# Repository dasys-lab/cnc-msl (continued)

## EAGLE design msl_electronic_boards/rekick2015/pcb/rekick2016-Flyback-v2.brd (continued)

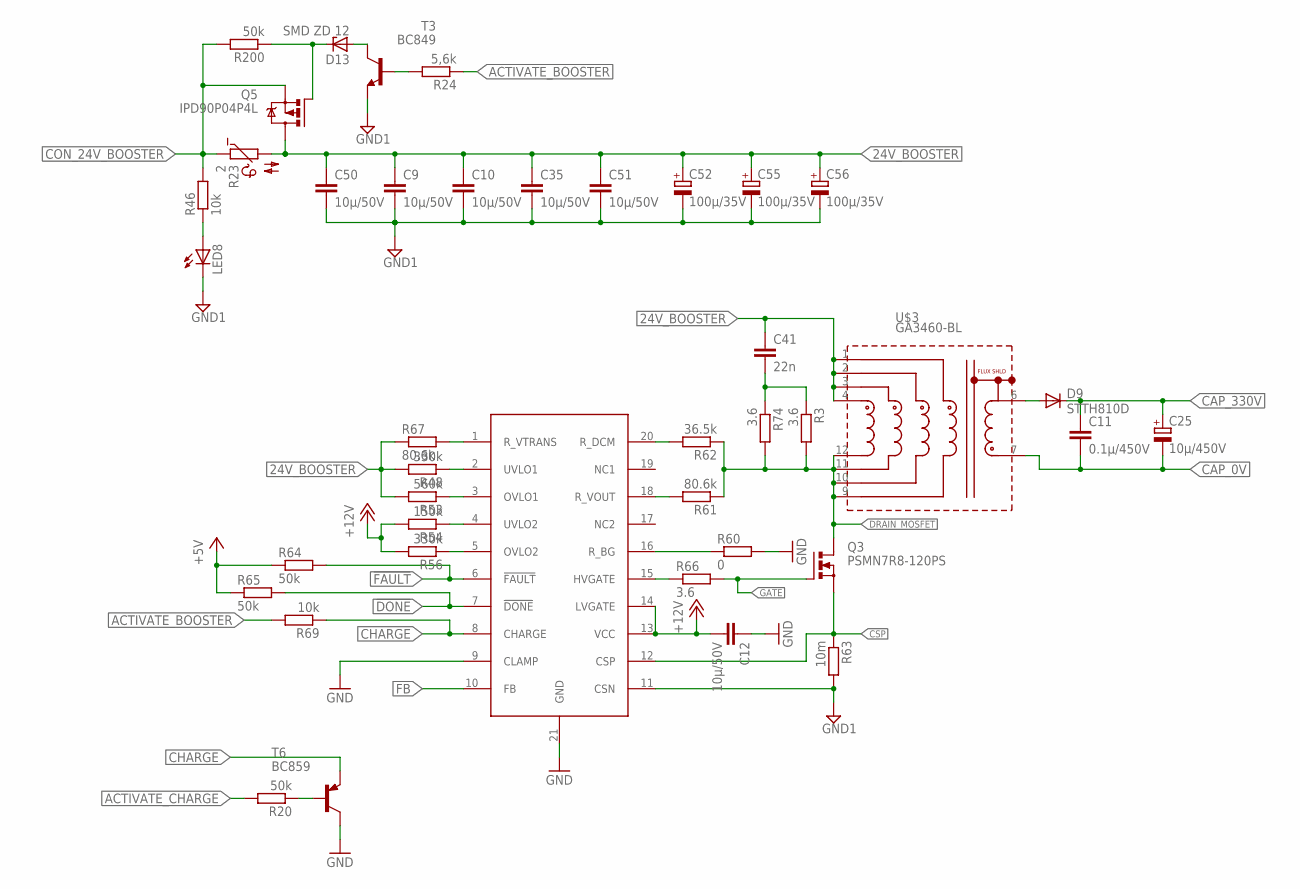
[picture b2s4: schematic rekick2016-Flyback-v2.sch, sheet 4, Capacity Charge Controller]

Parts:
C9, C10, C12, C35, C50, C51: 10µ/50V; C1206
C11: 0.1µ/450V; C2220K
C25: 10µ/450V; E5-10,5
C41: 22n; C1206
C52, C55, C56: 100µ/35V; E2,5-7
D9: STTH810D; TO220ACS
D13: SMD ZD 12; TO236
LED8: LEDCHIP-LED0805; CHIP-LED0805
Q3: PSMN7R8-120PS; TO220BV
Q5: IPD90P04P4L; D-PAK_TO252AA
R3, R66, R74: 3.6; R2010
R20, R64, R65, R200: 50k; R0805
R23: 2; N644A
R24: 5,6k; R0805
R46, R69: 10k; R0805
R48, R56: 330k; R0805
R53: 560k; R0805
R54: 150k; R0805
R60: 0; R0805
R61, R67: 80.6k; R0805
R62: 36.5k; R0805
R63: 10m; R2818
T3: BC849; SOT23
T6: BC859; SOT23-BEC
U$3: GA3460-BL; GA3459
U$9: LT3751; TSSOP20

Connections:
24V_BOOSTER: C9.1, C10.1, C35.1, C41.1, C50.1, C51.1, C52.+, C55.+, C56.+, Q5.4 (D), R23.2, R48.2, R53.2, R67.1, U$3.1 (W11), U$3.2 (W21), U$3.3 (W31), U$3.4 (W41); also elsewhere on the board
!DONE: R65.2, U$9.7 (!DONE); also elsewhere on the board
!FAULT: R64.2, U$9.6 (!FAULT); also elsewhere on the board
+5V: R64.1, R65.1; also elsewhere on the board
+12V: C12.2, R54.2, R56.2, U$9.13 (VCC), U$9.14 (LVGATE); also elsewhere on the board
ACTIVATE_BOOSTER: R24.1, R69.2; also elsewhere on the board
ACTIVATE_CHARGE: R20.2; also elsewhere on the board
CAP_0V: C11.2, C25.-, U$3.7 (S2); also elsewhere on the board
CAP_330V: C11.1, C25.+, D9.C; also elsewhere on the board
CHARGE: R69.1, T6.E, U$9.8 (CHARGE); also elsewhere on the board
CON_24V_BOOSTER: Q5.3 (S), R23.1, R46.2, R200.2; also elsewhere on the board
CSP: Q3.S, R63.P$1 (1), U$9.12 (CSP); also elsewhere on the board
DRAIN_MOSFET: Q3.D, R3.2, R61.1, R62.1, R74.2, U$3.9 (W12), U$3.10 (W22), U$3.11 (W32), U$3.12 (W42); also elsewhere on the board
FB: U$9.10 (FB); also elsewhere on the board
GATE: Q3.G, R66.2; also elsewhere on the board
GND: C12.1, R60.2, T6.C, U$9.9 (CLAMP), U$9.21 (GND); also elsewhere on the board
GND1: C9.2, C10.2, C35.2, C50.2, C51.2, C52.-, C55.-, C56.-, LED8.C, R63.P$2 (2), T3.2 (E), U$9.11 (CSN); also elsewhere on the board
unnamed: R60.1, U$9.16 (R_BG)
unnamed: R66.1, U$9.15 (HVGATE)
unnamed: R20.1, T6.B
unnamed: D9.A, U$3.6 (S1)
unnamed: R67.2, U$9.1 (R_VTRANS)
unnamed: R61.2, U$9.18 (R_VOUT)
unnamed: R62.2, U$9.20 (R_DCM)
unnamed: R54.1, U$9.4 (UVLO2)
unnamed: R53.1, U$9.3 (OVLO1)
unnamed: D13.C, Q5.1 (G), R200.1
unnamed: D13.A, T3.3 (C)
unnamed: R24.2, T3.1 (B)
unnamed: R56.1, U$9.5 (OVLO2)
unnamed: R48.1, U$9.2 (UVLO1)
unnamed: LED8.A, R46.1
unnamed: C41.2, R3.1, R74.1

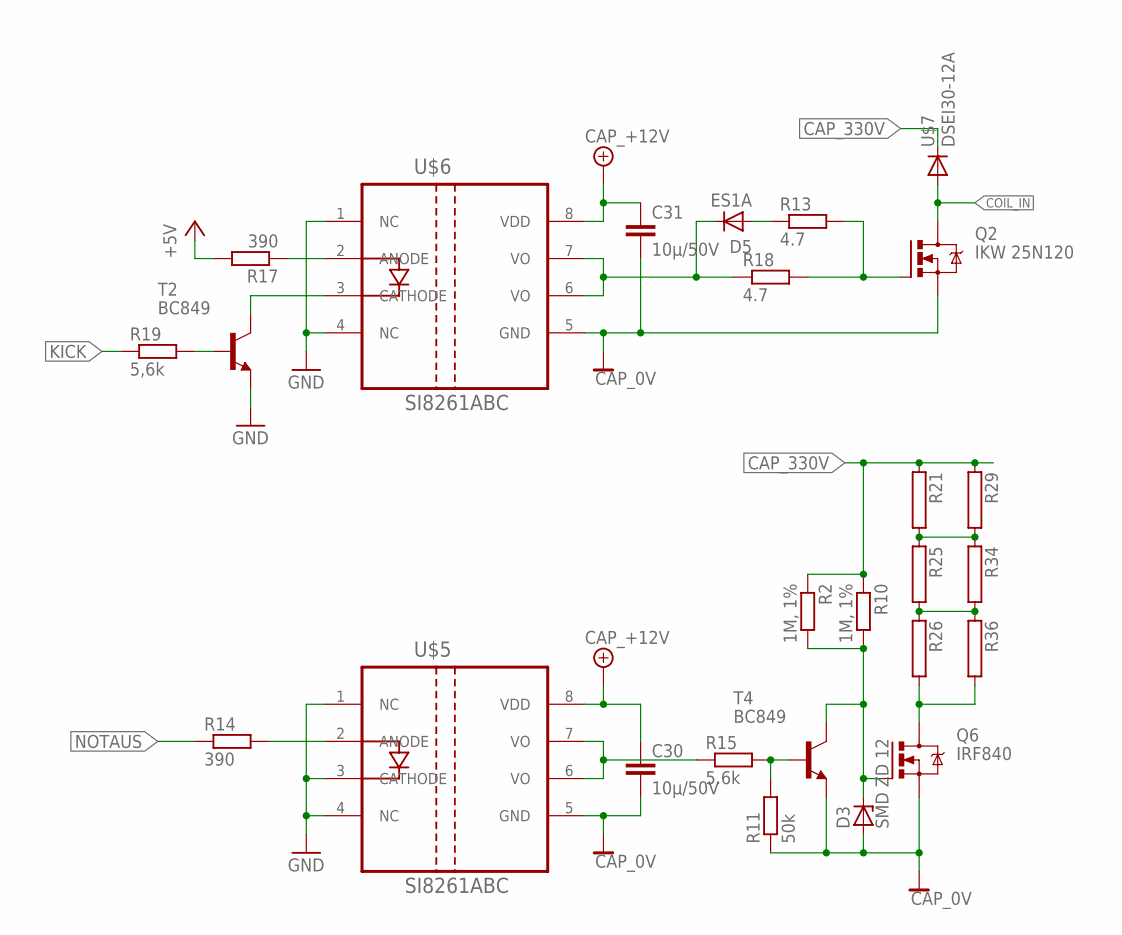
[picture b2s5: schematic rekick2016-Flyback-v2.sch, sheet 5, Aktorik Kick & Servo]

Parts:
C30, C31: 10µ/50V; C1206
D3: SMD ZD 12; TO236
D5: ES1A; SMA-DO214AC
Q2: IKW 25N120; TO247BV
Q6: IRF840; TO220BV
R2, R10: 1M, 1%; R1206
R11: 50k; R0805
R13, R18: 4.7; R0805
R14, R17: 390; R0805
R15: 5.6k; R0805
R19: 5,6k; R0805
R21, R25, R26, R29, R34, R36: RKH214-8R; KH214R-8
T2, T4: BC849; SOT23
U$5, U$6: SI8261ABC; SOIC-8
U$7: DSEI30-12A; TO247AD

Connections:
+5V: R17.2; also elsewhere on the board
CAP_0V: C30.2, C31.2, D3.A, Q2.S, Q6.S, R11.1, T4.2 (E), U$5.5 (GND), U$6.5 (GND); also elsewhere on the board
CAP_330V: R2.1, R10.1, R21.1, R29.1, U$7.C; also elsewhere on the board
CAP_+12V: C30.1, C31.1, U$5.8 (VDD), U$6.8 (VDD); also elsewhere on the board
COIL_IN: Q2.D, U$7.A; also elsewhere on the board
GND: T2.2 (E), U$5.1 (NC), U$5.3 (CATHODE), U$5.4 (NC), U$6.1 (NC), U$6.4 (NC); also elsewhere on the board
KICK: R19.1; also elsewhere on the board
unnamed: R25.2, R26.1, R34.2, R36.1
unnamed: R21.2, R25.1, R29.2, R34.1
unnamed: D3.C, Q6.G, R2.2, R10.2, T4.3 (C)
unnamed: R14.2, U$5.2 (ANODE)
unnamed: R15.1, U$5.6 (VO), U$5.7 (VO)
unnamed: R17.1, U$6.2 (ANODE)
unnamed: D5.K (C), R18.1, U$6.6 (VO), U$6.7 (VO)
unnamed: T2.3 (C), U$6.3 (CATHODE)
unnamed: R11.2, R15.2, T4.1 (B)
unnamed: R19.2, T2.1 (B)
unnamed: Q2.G, R13.2, R18.2
unnamed: Q6.D, R26.2, R36.2
unnamed: D5.A, R13.1
NOTAUS: R14.1; also elsewhere on the board

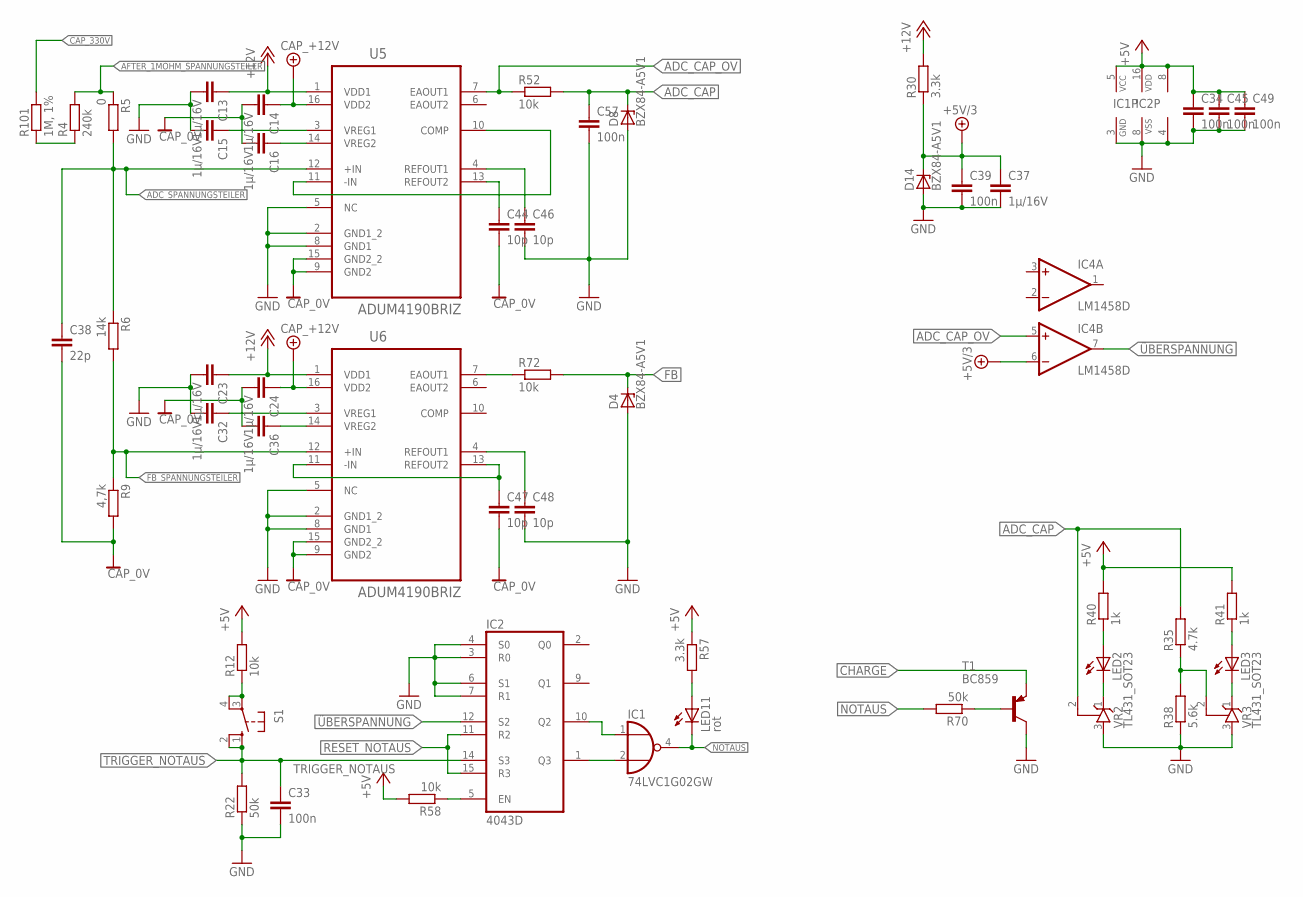
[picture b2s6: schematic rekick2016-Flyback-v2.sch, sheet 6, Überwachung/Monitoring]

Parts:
C13, C14, C15, C16, C23, C24, C32, C36, C37: 1µ/16V; C0603
C33, C34, C39, C45, C49, C57: 100n; C0603
C38: 22p; C0603
C44, C46, C47, C48: 10p; C0603
D4, D8, D14: BZX84-A5V1; TO236
IC1: 74LVC1G02GW; SOT23-5
IC2: 4043D; SO16
IC4: LM1458D; SO08
LED2, LED3: LEDCHIP-LED0805; CHIP-LED0805
LED11: rot; CHIPLED_0603
R4: 240k; R0805
R5: 0; R0805
R6: 14k; R0805
R9: 4,7k; R0805
R12, R52, R58, R72: 10k; R0805
R22, R70: 50k; R0805
R30, R57: 3.3k; R0805
R35: 4.7k; R0805
R38: 5.6k; R0805
R40, R41: 1k; R0805
R101: 1M, 1%; R1206
S1: 10-XX; B3F-10XX
T1: BC859; SOT23-BEC
U5, U6: ADUM4190BRIZ; SOIC127P1032X265-16N
VR2, VR3: TL431_SOT23; SOT23

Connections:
+5V: C34.1, C45.1, C49.1, IC1.5 (VCC), IC2.16 (VDD), IC4.8 (V+), R12.2, R40.2, R41.2, R57.1, R58.2; also elsewhere on the board
+5V/3: C37.1, C39.1, D14.C, IC4.6 (-IN), R30.1
+12V: C13.1, C23.1, R30.2, U5.1 (VDD1), U6.1 (VDD1); also elsewhere on the board
ADC_CAP: C57.1, D8.C, R35.2, R52.2, VR2.2 (R); also elsewhere on the board
ADC_CAP_OV: IC4.5 (+IN), R52.1, U5.7 (EAOUT1)
ADC_SPANNUNGSTEILER: C38.1, R5.2, R6.1, U5.12 (+IN); also elsewhere on the board
AFTER_1MOHM_SPANNUNGSTEILER: R4.2, R5.1; also elsewhere on the board
CAP_0V: C14.2, C16.2, C24.2, C36.2, C38.2, C44.2, C47.2, R9.2, U5.9 (GND2), U5.15 (GND2_2), U6.9 (GND2), U6.15 (GND2_2); also elsewhere on the board
CAP_330V: R101.2; also elsewhere on the board
CAP_+12V: C14.1, C24.1, U5.16 (VDD2), U6.16 (VDD2); also elsewhere on the board
CHARGE: T1.E; also elsewhere on the board
FB: D4.C, R72.2; also elsewhere on the board
FB_SPANNUNGSTEILER: R6.2, R9.1, U6.12 (+IN); also elsewhere on the board
GND: C13.2, C15.2, C23.2, C32.2, C33.2, C34.2, C37.2, C39.2, C45.2, C46.2, C48.2, C49.2, C57.2, D4.A, D8.A, D14.A, IC1.3 (GND), IC2.3 (R0), IC2.4 (S0), IC2.6 (S1), IC2.7 (R1), IC2.8 (VSS), IC4.4 (V-), R22.1, R38.1, T1.C, U5.2 (GND1_2), U5.5 (NC), U5.8 (GND1), U6.2 (GND1_2), U6.5 (NC), U6.8 (GND1), VR2.3 (A), VR3.3 (A); also elsewhere on the board
unnamed: R4.1, R101.1
unnamed: U5.10 (COMP), U5.11 (-IN)
unnamed: R12.1, S1.3, S1.4 (P1)
unnamed: IC1.1 (I0), IC2.10 (Q2)
unnamed: IC1.2 (I1), IC2.1 (Q3)
unnamed: IC2.5 (EN), R58.1
unnamed: C15.1, U5.3 (VREG1)
unnamed: C16.1, U5.14 (VREG2)
unnamed: C36.1, U6.14 (VREG2)
unnamed: R35.1, R38.2, VR3.2 (R)
unnamed: LED2.C, VR2.1 (C)
unnamed: LED3.C, VR3.1 (C)
unnamed: LED2.A, R40.1
unnamed: LED3.A, R41.1
unnamed: C32.1, U6.3 (VREG1)
unnamed: LED11.A, R57.2
unnamed: R70.1, T1.B
unnamed: C47.1, U6.11 (-IN), U6.13 (REFOUT2)
unnamed: C44.1, U5.13 (REFOUT2)
unnamed: C46.1, U5.4 (REFOUT1)
unnamed: R72.1, U6.7 (EAOUT1)
unnamed: C48.1, U6.4 (REFOUT1)
NOTAUS: IC1.4 (O), LED11.C, R70.2; also elsewhere on the board
RESET_NOTAUS: IC2.11 (R2), IC2.15 (R3); also elsewhere on the board
TRIGGER_NOTAUS: C33.1, IC2.14 (S3), R22.2, S1.1 (S), S1.2 (S1); also elsewhere on the board
ÜBERSPANNUNG: IC2.12 (S2), IC4.7 (OUT)

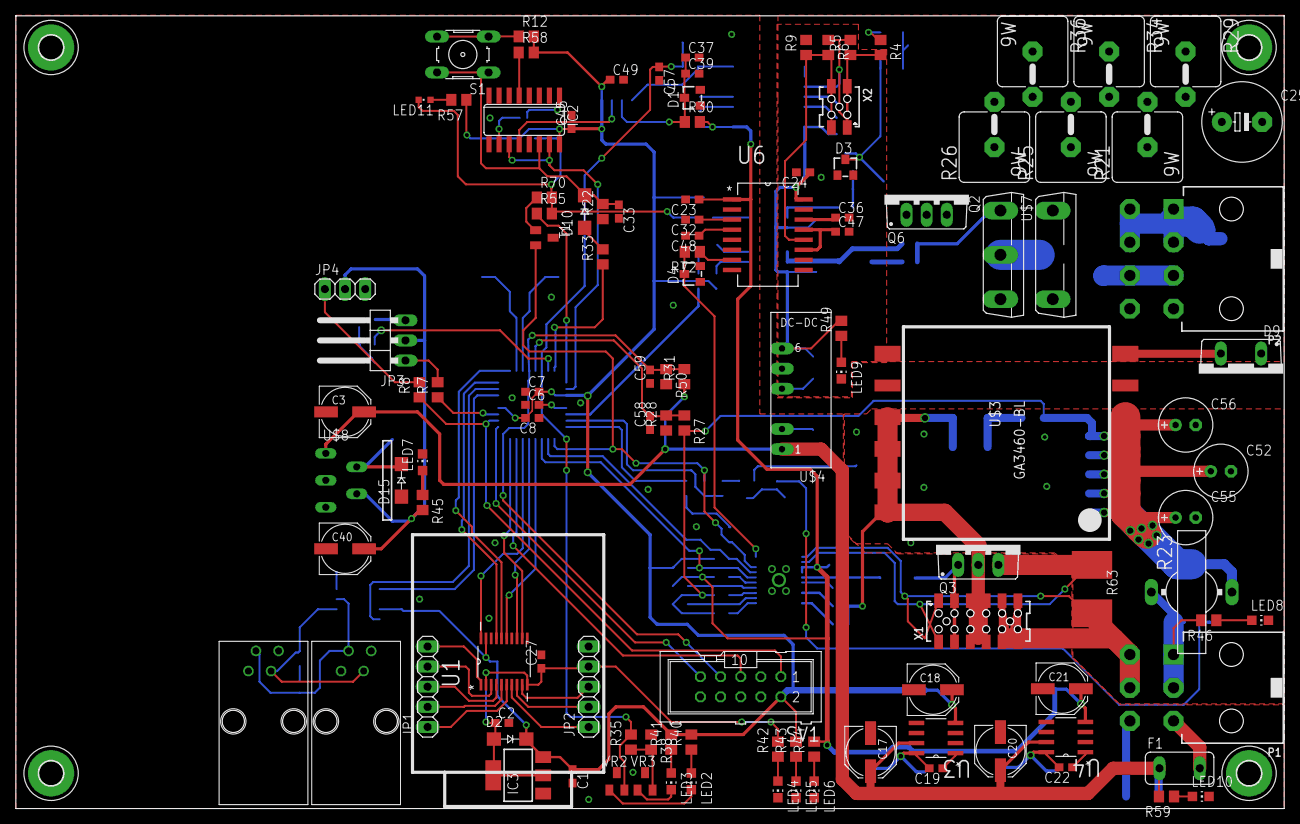
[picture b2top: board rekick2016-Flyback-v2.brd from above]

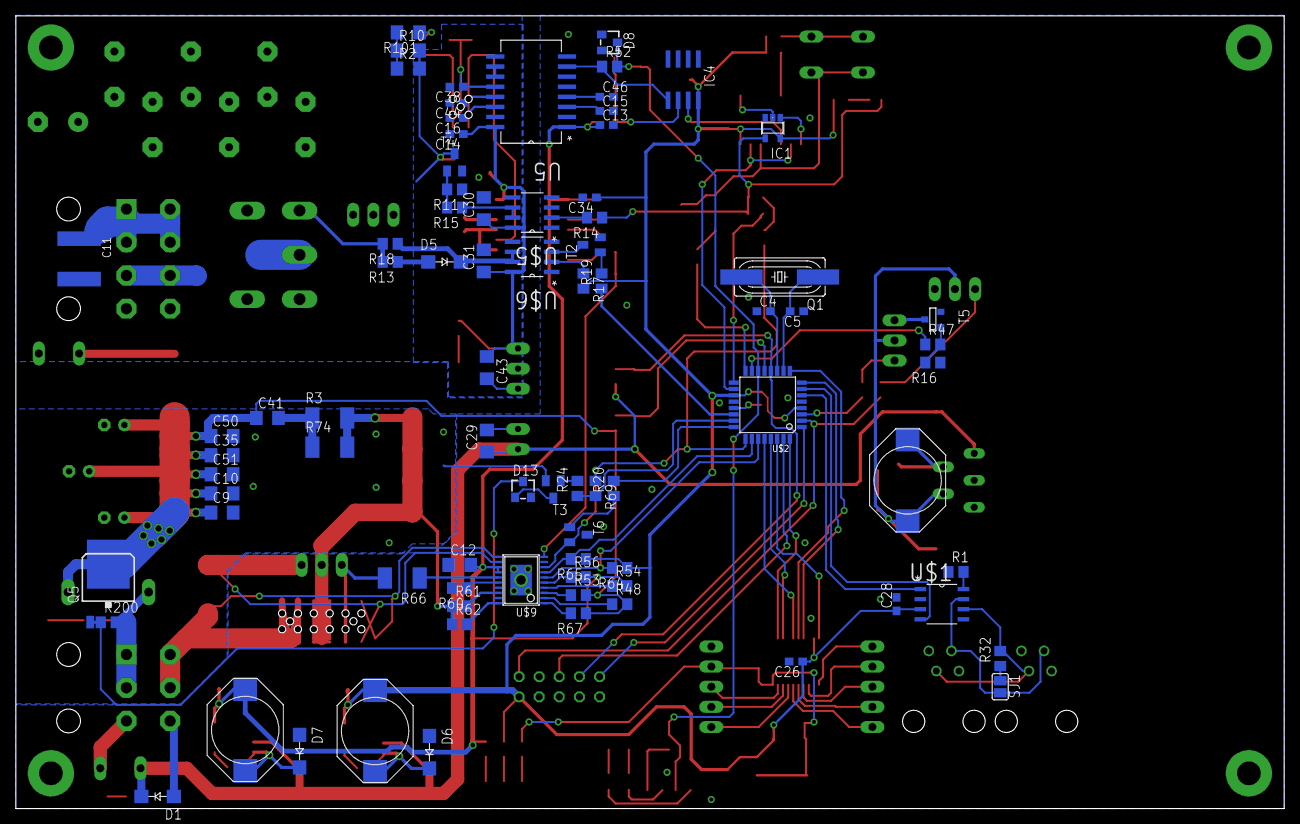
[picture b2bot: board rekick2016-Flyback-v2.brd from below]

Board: 4 copper layers, 160.0 x 100.0 mm, 201 parts (81 on the bottom side), 133 nets.

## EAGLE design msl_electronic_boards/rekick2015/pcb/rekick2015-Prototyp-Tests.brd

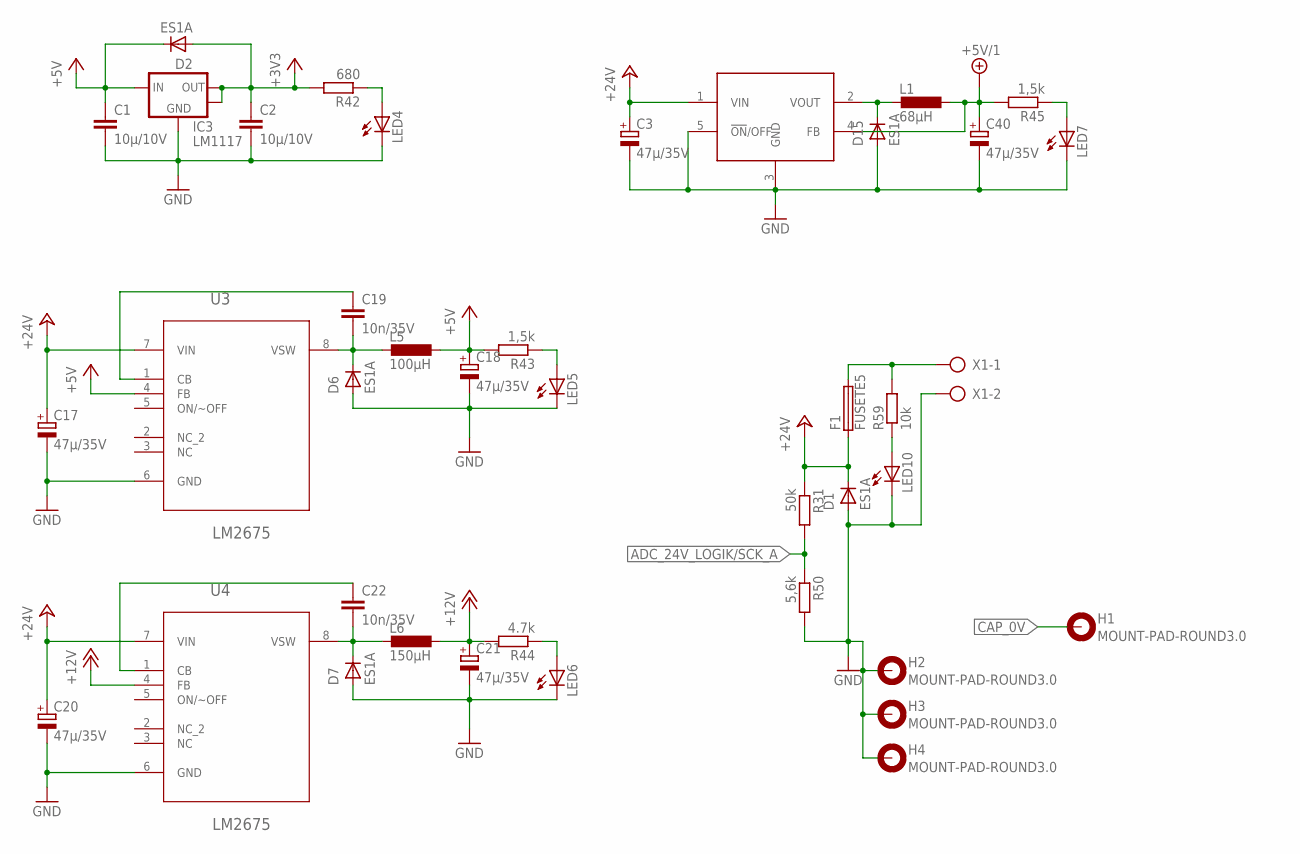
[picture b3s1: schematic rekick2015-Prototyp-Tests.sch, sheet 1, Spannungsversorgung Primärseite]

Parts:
C1, C2: 10µ/10V; C0603
C3, C17, C18, C20, C21, C40: 47µ/35V; PANASONIC_D
C19, C22: 10n/35V; C0603
D1, D2, D6, D7, D15: ES1A; SMA-DO214AC
F1: FUSETE5; TE5
H1, H2, H3, H4: MOUNT-PAD-ROUND3.0; 3,0-PAD
IC3: LM1117; SOT223
L1: 68µH; PISM
L5: 100µH; PISM
L6: 150µH; PISM
LED4, LED5, LED6, LED7, LED10: LEDCHIP-LED0805; CHIP-LED0805
R31: 50k; R0805
R42: 680; R0805
R43, R45: 1,5k; R0805
R44: 4.7k; R0805
R50: 5,6k; R0805
R59: 10k; R0805
U3, U4: LM2675; SOIC127P620X175-8N
U$8: LM2576; TO220511
X1: AK500/2-H

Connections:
+3V3: C2.1, D2.A, IC3.2 (OUT), IC3.4 (OUT), R42.2; also elsewhere on the board
+5V: C1.1, C18.+, D2.K (C), IC3.3 (IN), L5.1, R43.2, U3.4 (FB); also elsewhere on the board
+5V/1: C40.+, L1.1, R45.2, U$8.4 (FB); also elsewhere on the board
+12V: C21.+, L6.1, R44.2, U4.4 (FB); also elsewhere on the board
+24V: C3.+, C17.+, C20.+, D1.K (C), F1.1, R31.1, U3.7 (VIN), U4.7 (VIN), U$8.1 (VIN); also elsewhere on the board
ADC_24V_LOGIK/SCK_A: R31.2, R50.1; also elsewhere on the board
CAP_0V: H1.B3,0; also elsewhere on the board
GND: C1.2, C2.2, C3.-, C17.-, C18.-, C20.-, C21.-, C40.-, D1.A, D6.A, D7.A, D15.A, H2.B3,0, H3.B3,0, H4.B3,0, IC3.1 (GND), LED4.C, LED5.C, LED6.C, LED7.C, LED10.C, R50.2, U3.6 (GND), U4.6 (GND), U$8.3 (GND), U$8.5 (!ON!/OFF), X1.2; also elsewhere on the board
unnamed: C19.2, D6.K (C), L5.2, U3.8 (VSW)
unnamed: C19.1, U3.1 (CB)
unnamed: C22.2, D7.K (C), L6.2, U4.8 (VSW)
unnamed: F1.2, R59.2, X1.1
unnamed: C22.1, U4.1 (CB)
unnamed: LED4.A, R42.1
unnamed: D15.K (C), L1.2, U$8.2 (VOUT)
unnamed: LED7.A, R45.1
unnamed: LED5.A, R43.1
unnamed: LED6.A, R44.1
unnamed: LED10.A, R59.1

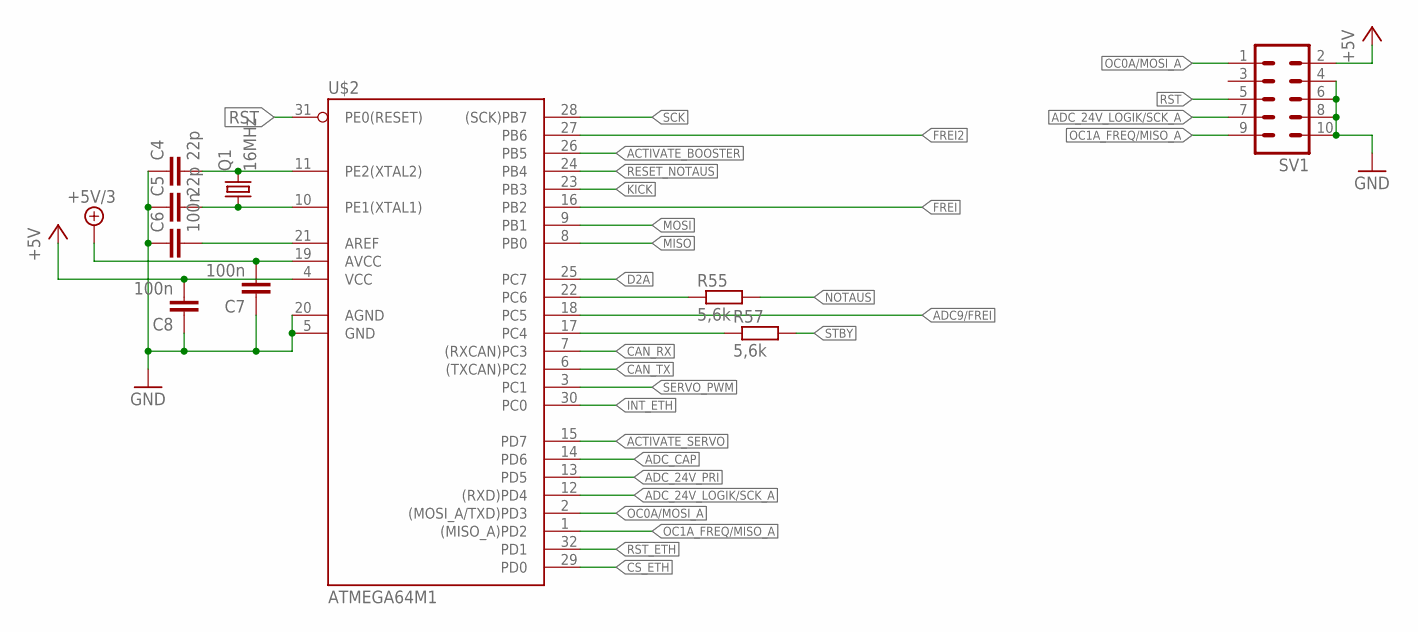
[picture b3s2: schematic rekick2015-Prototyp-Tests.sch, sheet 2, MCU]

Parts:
C4, C5: 22p; C0603
C6, C7, C8: 100n; C0603
Q1: 16MHz; HC49UP
R55, R57: 5,6k; R0805
SV1: ML10
U$2: ATMEGA64M1; TQFP32-08

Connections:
+5V: C8.2, SV1.2, U$2.4 (VCC); also elsewhere on the board
+5V/3: C7.2, U$2.19 (AVCC); also elsewhere on the board
ACTIVATE_BOOSTER: U$2.26 (PB5); also elsewhere on the board
ACTIVATE_SERVO: U$2.15 (PD7); also elsewhere on the board
ADC9/FREI: U$2.18 (PC5)
ADC_24V_LOGIK/SCK_A: SV1.7, U$2.12 ((RXD)PD4); also elsewhere on the board
ADC_24V_PRI: U$2.13 (PD5); also elsewhere on the board
ADC_CAP: U$2.14 (PD6); also elsewhere on the board
CAN_RX: U$2.7 ((RXCAN)PC3); also elsewhere on the board
CAN_TX: U$2.6 ((TXCAN)PC2); also elsewhere on the board
CS_ETH: U$2.29 (PD0); also elsewhere on the board
D2A: U$2.25 (PC7); also elsewhere on the board
FREI: U$2.16 (PB2)
FREI2: U$2.27 (PB6)
GND: C4.1, C5.1, C6.1, C7.1, C8.1, SV1.4, SV1.6, SV1.8, SV1.10, U$2.5 (GND), U$2.20 (AGND); also elsewhere on the board
INT_ETH: U$2.30 (PC0); also elsewhere on the board
KICK: U$2.23 (PB3); also elsewhere on the board
MISO: U$2.8 (PB0); also elsewhere on the board
MOSI: U$2.9 (PB1); also elsewhere on the board
unnamed: C4.2, Q1.2, U$2.11 (PE2(XTAL2))
unnamed: C5.2, Q1.1, U$2.10 (PE1(XTAL1))
unnamed: C6.2, U$2.21 (AREF)
unnamed: R55.1, U$2.22 (PC6)
unnamed: R57.1, U$2.17 (PC4)
NOTAUS: R55.2; also elsewhere on the board
OC0A/MOSI_A: SV1.1, U$2.2 ((MOSI_A/TXD)PD3); also elsewhere on the board
OC1A_FREQ/MISO_A: SV1.9, U$2.1 ((MISO_A)PD2); also elsewhere on the board
RESET_NOTAUS: U$2.24 (PB4); also elsewhere on the board
RST: SV1.5, U$2.31 (PE0(RESET))
RST_ETH: U$2.32 (PD1); also elsewhere on the board
SCK: U$2.28 ((SCK)PB7); also elsewhere on the board
SERVO_PWM: U$2.3 (PC1); also elsewhere on the board
STBY: R57.2; also elsewhere on the board

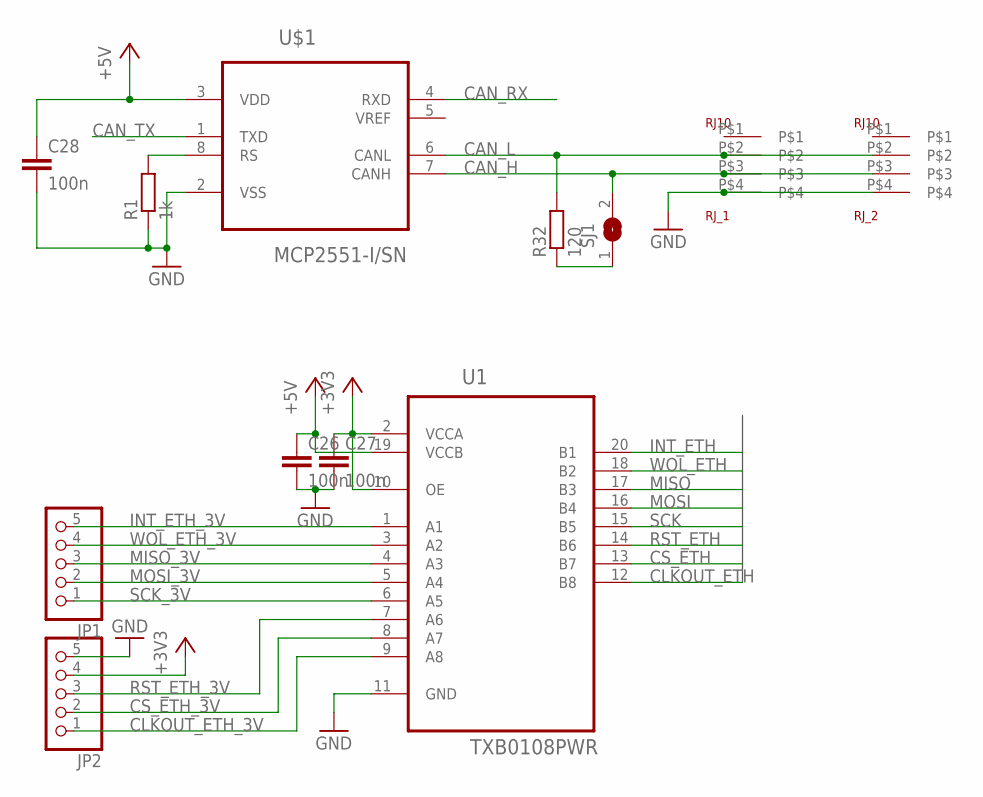
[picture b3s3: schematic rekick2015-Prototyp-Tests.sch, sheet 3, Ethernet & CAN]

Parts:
C26, C27, C28: 100n; C0603
JP1, JP2: PINHD-1X5; 1X05
R1: 1k; R0805
R32: 120; R0805
RJ_1, RJ_2: RJ10
SJ1: SJ
U1: TXB0108PWR; SOP65P640X120-20N
U$1: MCP2551-I/SN; SOIC127P600X175-8N

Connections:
+3V3: C27.1, JP2.4, U1.2 (VCCA), U1.10 (OE); also elsewhere on the board
+5V: C26.1, C28.1, U1.19 (VCCB), U$1.3 (VDD); also elsewhere on the board
CAN_H: RJ_1.P$3, RJ_2.P$3, SJ1.2, U$1.7 (CANH)
CAN_L: R32.2, RJ_1.P$2, RJ_2.P$2, U$1.6 (CANL)
CAN_RX: U$1.4 (RXD); also elsewhere on the board
CAN_TX: U$1.1 (TXD); also elsewhere on the board
CLKOUT_ETH: U1.12 (B8)
CLKOUT_ETH_3V: JP2.1, U1.9 (A8)
CS_ETH: U1.13 (B7); also elsewhere on the board
CS_ETH_3V: JP2.2, U1.8 (A7)
GND: C26.2, C27.2, C28.2, JP2.5, R1.1, RJ_1.P$4, RJ_2.P$4, U1.11 (GND), U$1.2 (VSS); also elsewhere on the board
INT_ETH: U1.20 (B1); also elsewhere on the board
INT_ETH_3V: JP1.5, U1.1 (A1)
MISO: U1.17 (B3); also elsewhere on the board
MISO_3V: JP1.3, U1.4 (A3)
MOSI: U1.16 (B4); also elsewhere on the board
MOSI_3V: JP1.2, U1.5 (A4)
unnamed: R1.2, U$1.8 (RS)
unnamed: R32.1, SJ1.1
RST_ETH: U1.14 (B6); also elsewhere on the board
RST_ETH_3V: JP2.3, U1.7 (A6)
SCK: U1.15 (B5); also elsewhere on the board
SCK_3V: JP1.1, U1.6 (A5)
WOL_ETH: U1.18 (B2)
WOL_ETH_3V: JP1.4, U1.3 (A2)

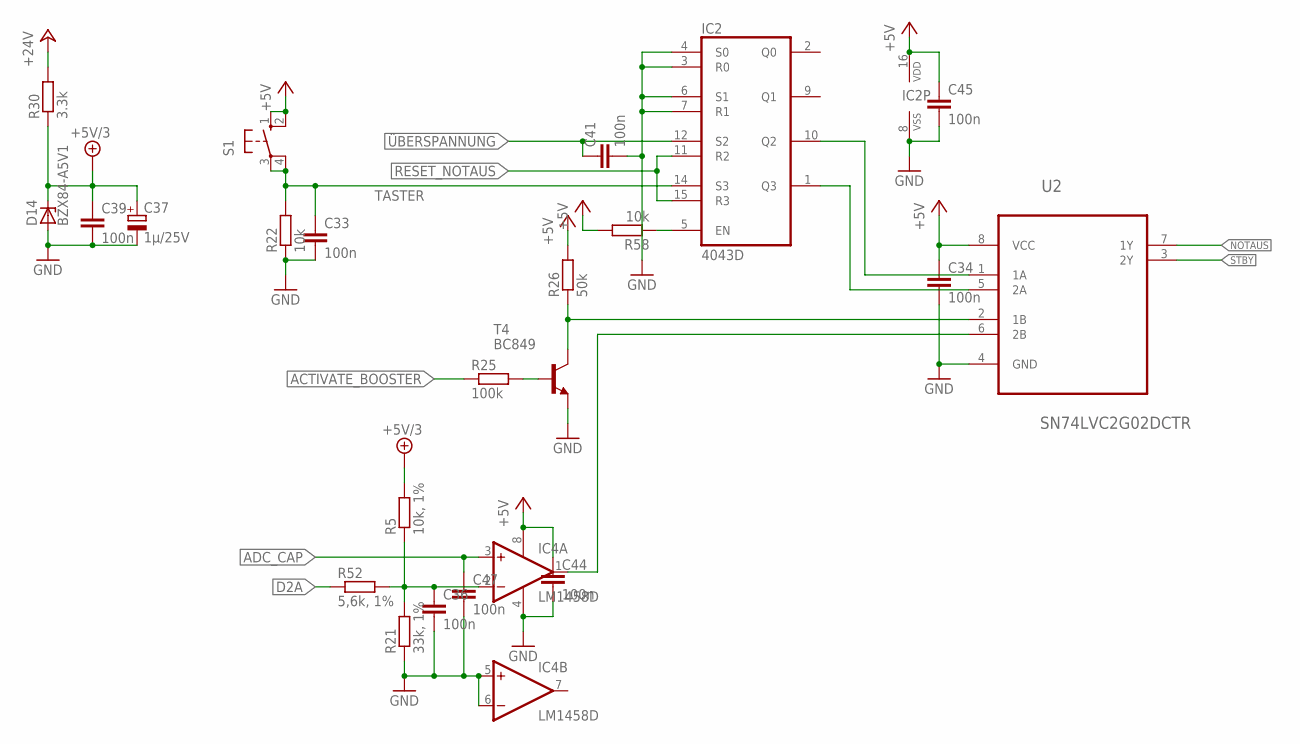
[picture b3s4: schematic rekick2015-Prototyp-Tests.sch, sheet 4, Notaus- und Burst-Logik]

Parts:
C33, C34, C36, C39, C41, C44, C45, C47: 100n; C0603
C37: 1µ/25V; SMC_A
D14: BZX84-A5V1; TO236
IC2: 4043D; SO16
IC4: LM1458D; SO08
R5: 10k, 1%; R0805
R21: 33k, 1%; R0805
R22, R58: 10k; R0805
R25: 100k; R0805
R26: 50k; R0805
R30: 3.3k; R0805
R52: 5,6k, 1%; R0805
S1: 10-XX; B3F-10XX
T4: BC849; SOT23
U2: SN74LVC2G02DCTR; SOP65P400X130-8N

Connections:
+5V: C34.1, C44.1, C45.1, IC2.16 (VDD), IC4.8 (V+), R26.2, R58.2, S1.1 (S), S1.2 (S1), U2.8 (VCC); also elsewhere on the board
+5V/3: C37.+, C39.1, D14.C, R5.2, R30.1; also elsewhere on the board
+24V: R30.2; also elsewhere on the board
ACTIVATE_BOOSTER: R25.1; also elsewhere on the board
ADC_CAP: C47.1, IC4.3 (+IN); also elsewhere on the board
D2A: R52.1; also elsewhere on the board
GND: C33.2, C34.2, C36.2, C37.-, C39.2, C41.2, C44.2, C45.2, C47.2, D14.A, IC2.3 (R0), IC2.4 (S0), IC2.6 (S1), IC2.7 (R1), IC2.8 (VSS), IC4.4 (V-), IC4.5 (+IN), IC4.6 (-IN), R21.1, R22.1, T4.2 (E), U2.4 (GND); also elsewhere on the board
KICK_VOLTAGE: C36.1, IC4.2 (-IN), R5.1, R21.2, R52.2
unnamed: IC2.10 (Q2), U2.1 (1A)
unnamed: IC2.1 (Q3), U2.5 (2A)
unnamed: IC2.5 (EN), R58.1
unnamed: IC4.1 (OUT), U2.6 (2B)
unnamed: R25.2, T4.1 (B)
unnamed: R26.1, T4.3 (C), U2.2 (1B)
NOTAUS: U2.7 (1Y); also elsewhere on the board
RESET_NOTAUS: IC2.11 (R2), IC2.15 (R3); also elsewhere on the board
STBY: U2.3 (2Y); also elsewhere on the board
TASTER: C33.1, IC2.14 (S3), R22.2, S1.3, S1.4 (P1)
ÜBERSPANNUNG: C41.1, IC2.12 (S2); also elsewhere on the board

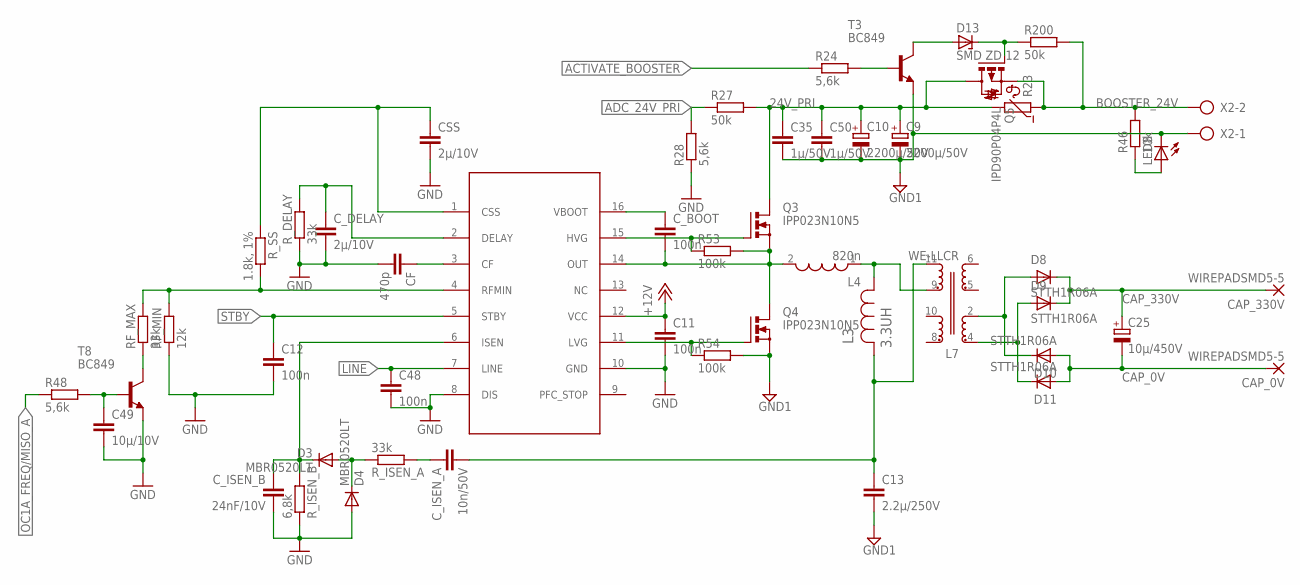
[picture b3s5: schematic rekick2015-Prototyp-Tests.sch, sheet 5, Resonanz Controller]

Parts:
C9, C10: 2200µ/50V; E5-13
C11, C12, C48: 100n; C0603
C13: 2.2µ/250V; C2220K
C25: 10µ/450V; E5-10,5
C35, C50: 1µ/50V; C1206
C49: 10µ/10V; C0603
CAP_0V, CAP_330V: WIREPADSMD5-5; 5-5
CF: 470p; C0603
CSS: 2µ/10V; C0603
C_BOOT: 100n; C0603
C_DELAY: 2µ/10V; C0603
C_ISEN_A: 10n/50V; C0603
C_ISEN_B: 24nF/10V; C0603
D3, D4: MBR0520LT; SOD123
D8, D9, D10, D11: STTH1R06A; SMA-DO214AC
D13: SMD ZD 12; TO236
L3: 3.3UH; IND_ELLATP-B
L4: 820n; WE-HCI_1890
L7: WE-LLCR; WE-LLCR_ETD34
LED8: LEDCHIP-LED0805; CHIP-LED0805
Q3, Q4: IPP023N10N5; TO220BV
Q5: IPD90P04P4L; D-PAK_TO252AA
R23: NTC644A; N644A
R24, R28, R48: 5,6k; R0805
R27, R200: 50k; R0805
R46: 10k; R0805
R53, R54: 100k; R0805
RF_MAX: 33k; R0805
RF_MIN: 12k; R0805
R_DELAY: 33k; R0805
R_ISEN_A: 33k; R0805
R_ISEN_B: 6,8k; R0805
R_SS: 1.8k, 1%; R0805
T3, T8: BC849; SOT23
U$3: L6599; SO16
X2: AK500/2-H

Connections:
24V_PRI: C9.+, C10.+, C35.1, C50.1, Q3.D, Q5.4 (D), R23.2, R27.2
+12V: C11.1, U$3.12 (VCC); also elsewhere on the board
ACTIVATE_BOOSTER: R24.1; also elsewhere on the board
ADC_24V_PRI: R27.1, R28.2; also elsewhere on the board
BOOSTER_24V: Q5.3 (S), R23.1, R46.2, R200.2, X2.2
CAP_0V: C25.-, CAP_0V.P$1, D10.A, D11.A; also elsewhere on the board
CAP_330V: C25.+, CAP_330V.P$1, D8.K (C), D9.K (C); also elsewhere on the board
GND: C11.2, C12.2, C48.2, C49.2, CF.2, CSS.2, C_DELAY.2, C_ISEN_B.2, D4.A, R28.1, RF_MIN.1, R_DELAY.1, R_ISEN_B.1, T8.2 (E), U$3.8 (DIS), U$3.10 (GND); also elsewhere on the board
GND1: C9.-, C10.-, C13.2, C35.2, C50.2, LED8.C, Q4.S, R54.2, T3.2 (E), X2.1
LINE: C48.1, U$3.7 (LINE); also elsewhere on the board
unnamed: RF_MAX.1, T8.3 (C)
unnamed: RF_MAX.2, RF_MIN.2, R_SS.2, U$3.4 (RFMIN)
unnamed: CF.1, U$3.3 (CF)
unnamed: Q3.G, R53.1, U$3.15 (HVG)
unnamed: Q4.G, R54.1, U$3.11 (LVG)
unnamed: CSS.1, R_SS.1, U$3.1 (CSS)
unnamed: C_BOOT.1, U$3.16 (VBOOT)
unnamed: C_DELAY.1, R_DELAY.2, U$3.2 (DELAY)
unnamed: C_ISEN_B.1, D3.C, R_ISEN_B.2, U$3.6 (ISEN)
unnamed: L3.1, L4.1, L7.9 (4)
unnamed: D3.A, D4.C, R_ISEN_A.1
unnamed: C_ISEN_A.1, R_ISEN_A.2
unnamed: D8.A, D10.K (C), L7.2 (8)
unnamed: D9.A, D11.K (C), L7.4 (1)
unnamed: D13.C, Q5.1 (G), R200.1
unnamed: D13.A, T3.3 (C)
unnamed: R24.2, T3.1 (B)
unnamed: LED8.A, R46.1
unnamed: C49.1, R48.2, T8.1 (B)
OC1A_FREQ/MISO_A: R48.1; also elsewhere on the board
STBY: C12.1, U$3.5 (STBY); also elsewhere on the board
TRAFO1: C_BOOT.2, L4.2, Q3.S, Q4.D, R53.2, U$3.14 (OUT)
TRAFO2: C13.1, C_ISEN_A.2, L3.2, L7.11 (5)

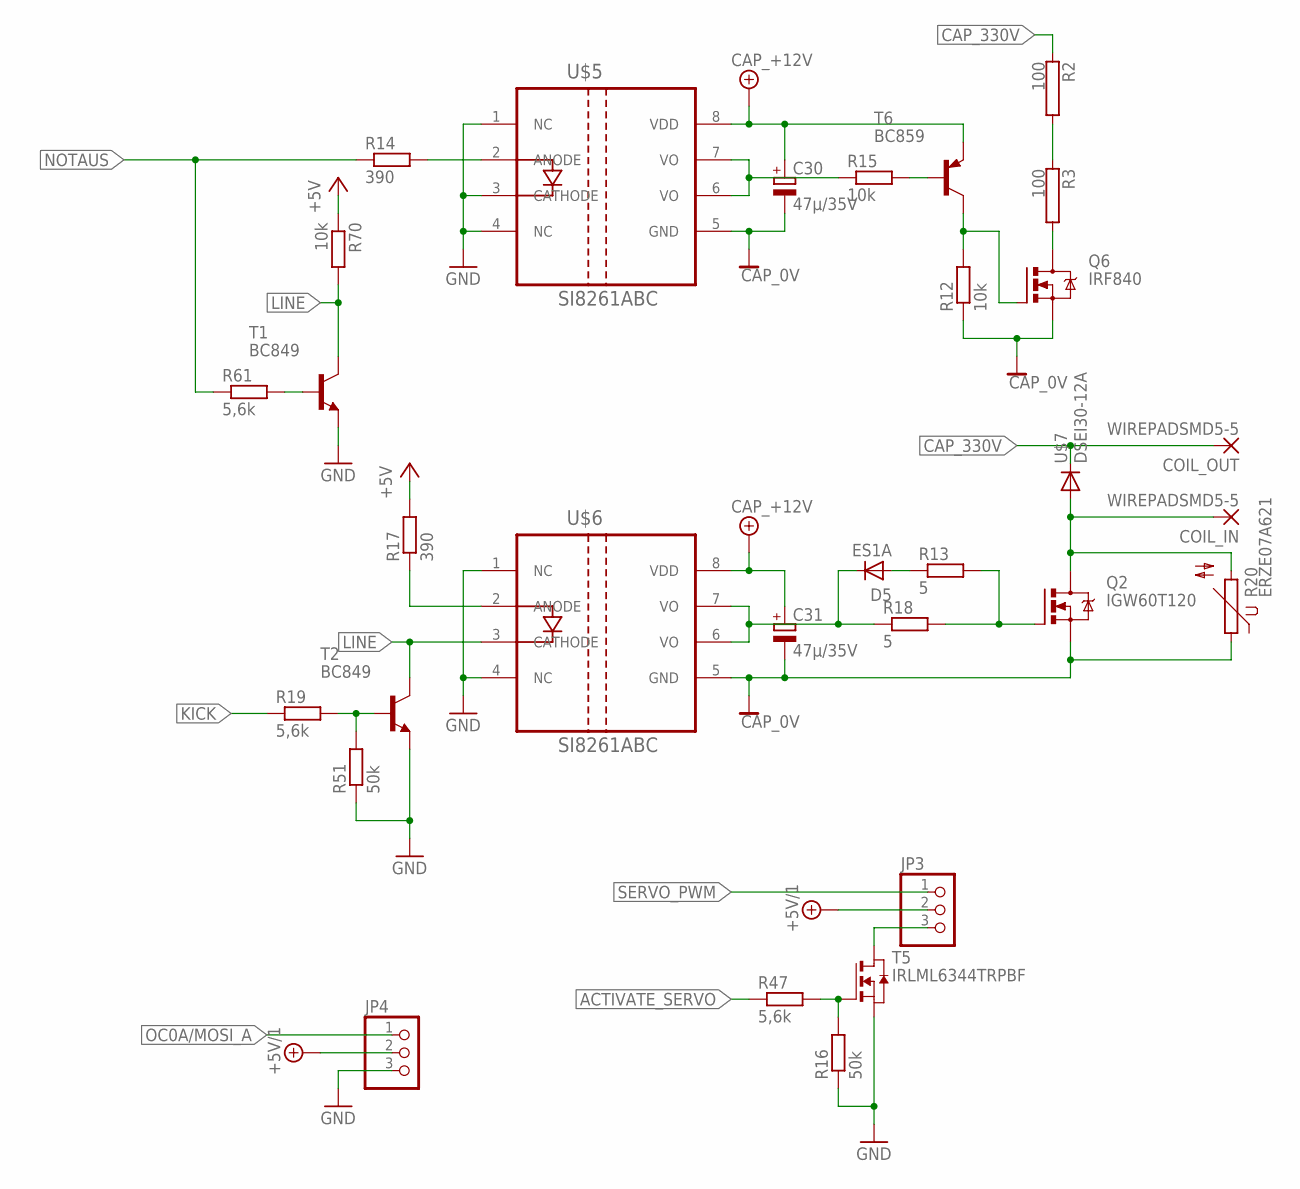
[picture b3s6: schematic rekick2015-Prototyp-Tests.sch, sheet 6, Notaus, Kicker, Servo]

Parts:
C30, C31: 47µ/35V; E2-5
COIL_IN: WIREPADSMD5-5; 5-5
COIL_OUT: WIREPADSMD5-5; 5-5
D5: ES1A; SMA-DO214AC
JP3, JP4: PINHD-1X3; 1X03
Q2: IGW60T120; TO247BV
Q6: IRF840; TO220BV
R2, R3: 100; HS25
R12, R15, R70: 10k; R0805
R13, R18: 5; R2512
R14, R17: 390; R0805
R16, R51: 50k; R0805
R19, R47, R61: 5,6k; R0805
R20: ERZE07A621; S10K385
T1, T2: BC849; SOT23
T5: IRLML6344TRPBF; SOT-23
T6: BC859; SOT23-BEC
U$5, U$6: SI8261ABC; SOIC-8
U$7: DSEI30-12A; TO247AD

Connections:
+5V: R17.2, R70.1; also elsewhere on the board
+5V/1: JP3.2, JP4.2; also elsewhere on the board
ACTIVATE_SERVO: R47.1; also elsewhere on the board
CAP_0V: C30.-, C31.-, Q2.S, Q6.S, R12.1, R20.1, U$5.5 (GND), U$6.5 (GND); also elsewhere on the board
CAP_330V: COIL_OUT.P$1, R2.1, U$7.C; also elsewhere on the board
CAP_+12V: C30.+, C31.+, T6.E, U$5.8 (VDD), U$6.8 (VDD); also elsewhere on the board
GND: JP4.3, R16.1, R51.1, T1.2 (E), T2.2 (E), T5.2 (S), U$5.1 (NC), U$5.3 (CATHODE), U$5.4 (NC), U$6.1 (NC), U$6.4 (NC); also elsewhere on the board
KICK: R19.1; also elsewhere on the board
LINE: R70.2, T1.3 (C), T2.3 (C), U$6.3 (CATHODE); also elsewhere on the board
unnamed: R2.2, R3.1
unnamed: Q6.D, R3.2
unnamed: Q6.G, R12.2, T6.C
unnamed: R14.2, U$5.2 (ANODE)
unnamed: R15.1, U$5.6 (VO), U$5.7 (VO)
unnamed: R17.1, U$6.2 (ANODE)
unnamed: D5.K (C), R18.1, U$6.6 (VO), U$6.7 (VO)
unnamed: R15.2, T6.B
unnamed: R19.2, R51.2, T2.1 (B)
unnamed: Q2.G, R13.2, R18.2
unnamed: COIL_IN.P$1, Q2.D, R20.2, U$7.A
unnamed: D5.A, R13.1
unnamed: JP3.3, T5.1 (D)
unnamed: R16.2, R47.2, T5.3 (G)
unnamed: R61.2, T1.1 (B)
NOTAUS: R14.1, R61.1; also elsewhere on the board
OC0A/MOSI_A: JP4.1; also elsewhere on the board
SERVO_PWM: JP3.1; also elsewhere on the board
